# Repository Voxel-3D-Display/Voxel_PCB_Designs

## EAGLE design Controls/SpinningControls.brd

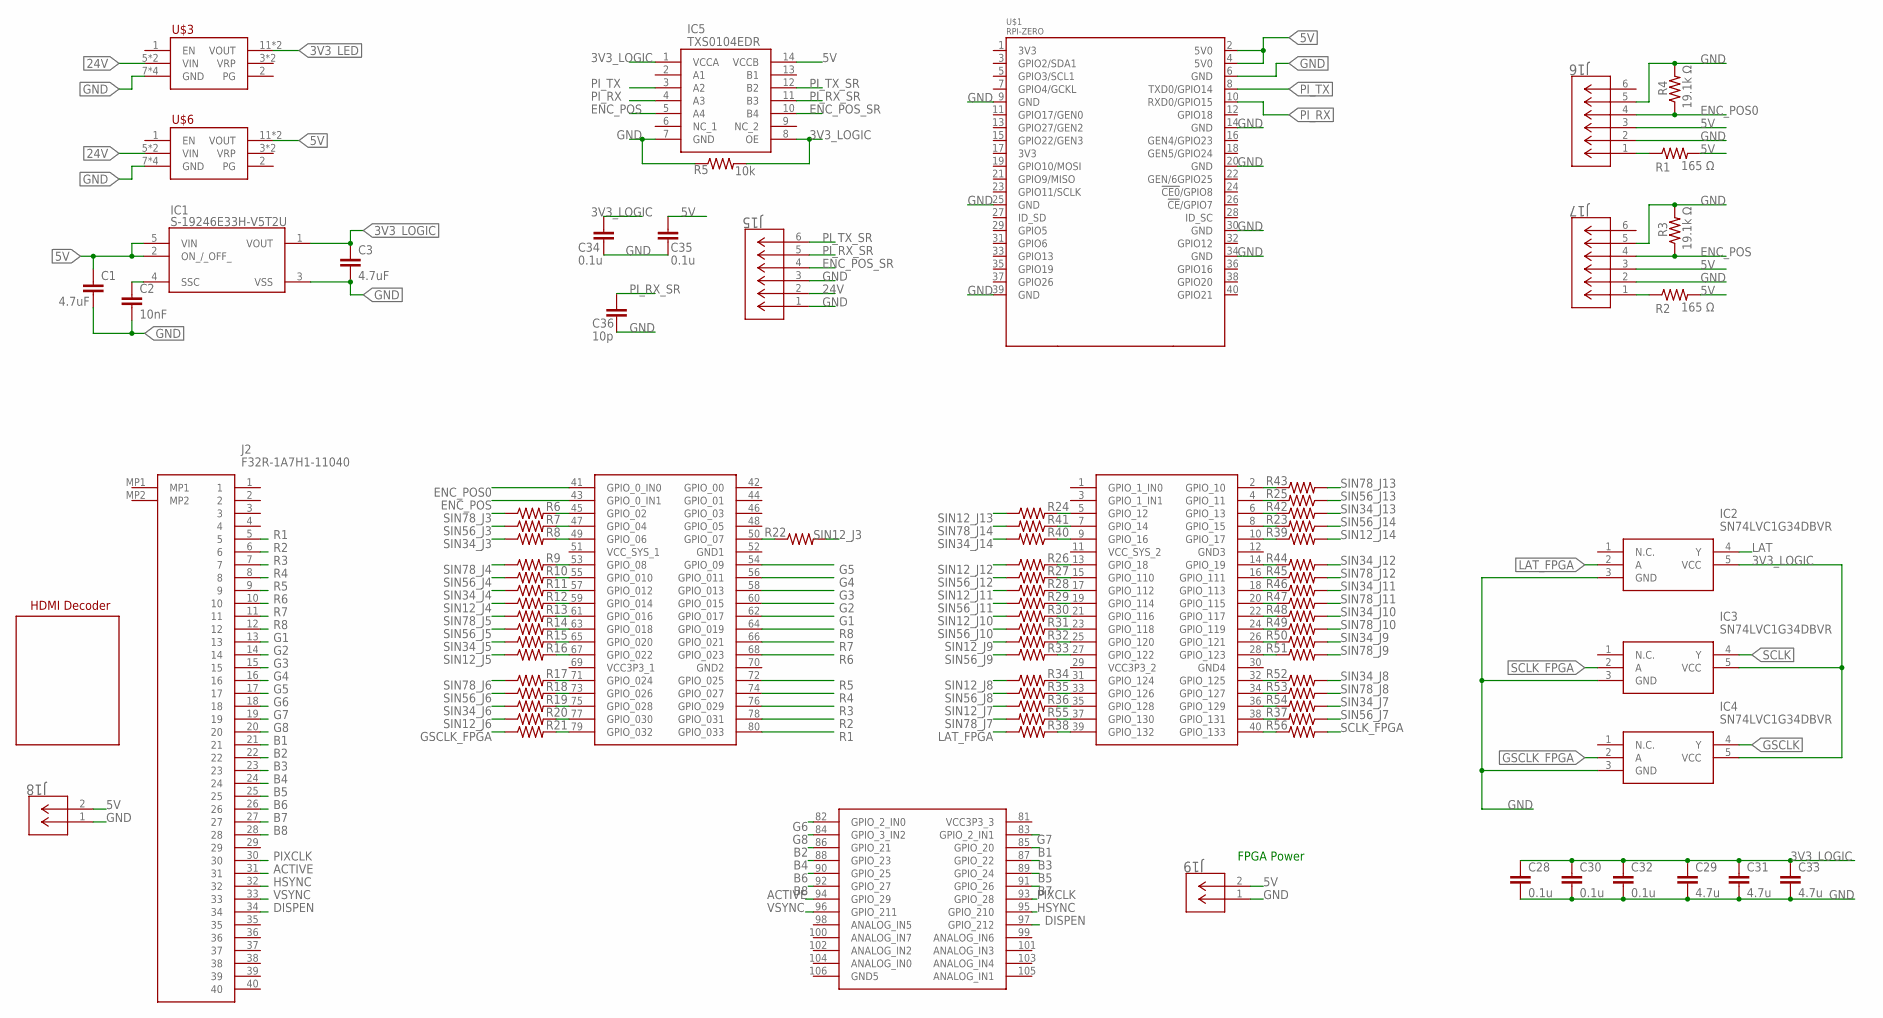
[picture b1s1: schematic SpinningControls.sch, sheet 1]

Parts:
C1, C3: 4.7uF; C0603
C2: 10nF; C0603
C28, C30, C32, C34, C35: 0.1u; C0603
C29, C31, C33: 4.7u; C0603
C36: 10p; C0603
FPGA: DE0-NANO
IC1: S-19246E33H-V5T2U; S19246E33HV5T2U
IC2, IC3, IC4: SN74LVC1G34DBVR; SOT95P280X145-5N
IC5: TXS0104EDR; SOIC127P600X175-14N
J2: F32R-1A7H1-11040; F32R1A7H111040
J15, J16, J17: 430450612; CON_430450612_MOL
J18, J19: 436500215; CON_436500215_MOL
R1, R2: 165 Ω; R0603
R3, R4: 19.1k Ω; R0603
R5: 10k; R0603
R6, R7, R8, R9, R10, R11, R12, R13, R14, R15, R16, R17, R18, R19, R20, R21, R22, R23, R24, R25, R26, R27, R28, R29, R30, R31, R32, R33, R34, R35, R36, R37, R38, R39, R40, R41, R42, R43, R44, R45, R46, R47, R48, R49, R50, R51, R52, R53, R54, R55, R56: R-US_R0402; R0402
U$1: RPI-ZERO; RASPBERRYPI_BASTELSTUBE_V13_RASPI_BOARD_B+_FULL
U$2: TFP401
U$3: 3V3_BUCK_REGULATOR; 2X06
U$6: 5V_BUCK_REGULATOR; 2X06

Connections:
3V3_LED: U$3.11 (VOUT), U$3.12 (VOUT); also elsewhere on the board
3V3_LOGIC: C3.1, C28.1, C29.1, C30.1, C31.1, C32.1, C33.1, C34.1, IC1.1 (VOUT), IC2.5 (VCC), IC3.5 (VCC), IC4.5 (VCC), IC5.1 (VCCA), IC5.8 (OE), R5.2; also elsewhere on the board
5V: C1.1, C35.1, IC1.2 (ON_/_OFF_), IC1.5 (VIN), IC5.14 (VCCB), J16.3, J17.3, J18.2, J19.2, R1.2, R2.2, U$1.2 (5V0), U$1.4 (5V0), U$6.11 (VOUT), U$6.12 (VOUT)
24V: J15.2, U$3.5 (VIN), U$3.6 (VIN), U$6.5 (VIN), U$6.6 (VIN)
ACTIVE: FPGA.94 (GPIO_29), J2.31
B1: FPGA.85 (GPIO_20), J2.21
B2: FPGA.86 (GPIO_21), J2.22
B3: FPGA.87 (GPIO_22), J2.23
B4: FPGA.88 (GPIO_23), J2.24
B5: FPGA.89 (GPIO_24), J2.25
B6: FPGA.90 (GPIO_25), J2.26
B7: FPGA.91 (GPIO_26), J2.27
B8: FPGA.92 (GPIO_27), J2.28
DISPEN: FPGA.97 (GPIO_212), J2.34
ENC_POS: FPGA.43 (GPIO_0_IN1), IC5.5 (A4), J17.4, R3.1
ENC_POS0: FPGA.41 (GPIO_0_IN0), J16.4, R4.1
ENC_POS_SR: IC5.10 (B4), J15.4
G1: FPGA.62 (GPIO_017), J2.13
G2: FPGA.60 (GPIO_015), J2.14
G3: FPGA.58 (GPIO_013), J2.15
G4: FPGA.56 (GPIO_011), J2.16
G5: FPGA.54 (GPIO_09), J2.17
G6: FPGA.82 (GPIO_2_IN0), J2.18
G7: FPGA.83 (GPIO_2_IN1), J2.19
G8: FPGA.84 (GPIO_3_IN2), J2.20
GND: C1.2, C2.2, C3.2, C28.2, C29.2, C30.2, C31.2, C32.2, C33.2, C34.2, C35.2, C36.2, IC1.3 (VSS), IC2.3 (GND), IC3.3 (GND), IC4.3 (GND), IC5.7 (GND), J15.1, J15.3, J16.2, J16.5, J17.2, J17.5, J18.1, J19.1, R3.2, R4.2, R5.1, U$1.6 (GND), U$1.9 (GND), U$1.14 (GND), U$1.20 (GND), U$1.25 (GND), U$1.30 (GND), U$1.34 (GND), U$1.39 (GND), U$3.7 (GND), U$3.8 (GND), U$3.9 (GND), U$3.10 (GND), U$6.7 (GND), U$6.8 (GND), U$6.9 (GND), U$6.10 (GND); also elsewhere on the board
GSCLK: IC4.4 (Y); also elsewhere on the board
GSCLK_FPGA: IC4.2 (A), R21.1
HSYNC: FPGA.95 (GPIO_210), J2.32
LAT: IC2.4 (Y); also elsewhere on the board
LAT_FPGA: IC2.2 (A), R38.1
unnamed: J16.1, R1.1
unnamed: FPGA.45 (GPIO_02), R6.2
unnamed: FPGA.50 (GPIO_07), R22.1
unnamed: C2.1, IC1.4 (SSC)
unnamed: FPGA.79 (GPIO_032), R21.2
unnamed: J17.1, R2.1
unnamed: FPGA.8 (GPIO_15), R23.2
unnamed: FPGA.5 (GPIO_12), R24.2
unnamed: FPGA.4 (GPIO_11), R25.2
unnamed: FPGA.9 (GPIO_16), R40.1
unnamed: FPGA.7 (GPIO_14), R41.1
unnamed: FPGA.6 (GPIO_13), R42.1
unnamed: FPGA.2 (GPIO_10), R43.1
unnamed: FPGA.13 (GPIO_18), R26.2
unnamed: FPGA.47 (GPIO_04), R7.2
unnamed: FPGA.49 (GPIO_06), R8.2
unnamed: FPGA.15 (GPIO_110), R27.2
unnamed: FPGA.53 (GPIO_08), R9.2
unnamed: FPGA.55 (GPIO_010), R10.2
unnamed: FPGA.57 (GPIO_012), R11.2
unnamed: FPGA.59 (GPIO_014), R12.2
unnamed: FPGA.61 (GPIO_016), R13.2
unnamed: FPGA.63 (GPIO_018), R14.2
unnamed: FPGA.65 (GPIO_020), R15.2
unnamed: FPGA.67 (GPIO_022), R16.2
unnamed: FPGA.17 (GPIO_112), R28.2
unnamed: FPGA.71 (GPIO_024), R17.2
unnamed: FPGA.73 (GPIO_026), R18.2
unnamed: FPGA.75 (GPIO_028), R19.2
unnamed: FPGA.77 (GPIO_030), R20.2
unnamed: FPGA.19 (GPIO_114), R29.2
unnamed: FPGA.21 (GPIO_116), R30.2
unnamed: FPGA.23 (GPIO_118), R31.2
unnamed: FPGA.25 (GPIO_120), R32.2
unnamed: FPGA.27 (GPIO_122), R33.2
unnamed: FPGA.31 (GPIO_124), R34.2
unnamed: FPGA.33 (GPIO_126), R35.2
unnamed: FPGA.35 (GPIO_128), R36.2
unnamed: FPGA.38 (GPIO_131), R37.2
unnamed: FPGA.39 (GPIO_132), R38.2
unnamed: FPGA.14 (GPIO_19), R44.1
unnamed: FPGA.16 (GPIO_111), R45.1
unnamed: FPGA.18 (GPIO_113), R46.1
unnamed: FPGA.20 (GPIO_115), R47.1
unnamed: FPGA.22 (GPIO_117), R48.1
unnamed: FPGA.24 (GPIO_119), R49.1
unnamed: FPGA.26 (GPIO_121), R50.1
unnamed: FPGA.28 (GPIO_123), R51.1
unnamed: FPGA.32 (GPIO_125), R52.1
unnamed: FPGA.34 (GPIO_127), R53.1
unnamed: FPGA.36 (GPIO_129), R54.1
unnamed: FPGA.37 (GPIO_130), R55.1
unnamed: FPGA.40 (GPIO_133), R56.1
unnamed: FPGA.10 (GPIO_17), R39.1
PIXCLK: FPGA.93 (GPIO_28), J2.30
PI_RX: IC5.4 (A3), U$1.10 (RXD0/GPIO15)
PI_RX_SR: C36.1, IC5.11 (B3), J15.5
PI_TX: IC5.3 (A2), U$1.8 (TXD0/GPIO14)
PI_TX_SR: IC5.12 (B2), J15.6
R1: FPGA.80 (GPIO_033), J2.5
R2: FPGA.78 (GPIO_031), J2.6
R3: FPGA.76 (GPIO_029), J2.7
R4: FPGA.74 (GPIO_027), J2.8
R5: FPGA.72 (GPIO_025), J2.9
R6: FPGA.68 (GPIO_023), J2.10
R7: FPGA.66 (GPIO_021), J2.11
R8: FPGA.64 (GPIO_019), J2.12
SCLK: IC3.4 (Y); also elsewhere on the board
SCLK_FPGA: IC3.2 (A), R56.2
SIN12_J3: R22.2; also elsewhere on the board
SIN12_J4: R12.1; also elsewhere on the board
SIN12_J5: R16.1; also elsewhere on the board
SIN12_J6: R20.1; also elsewhere on the board
SIN12_J7: R36.1; also elsewhere on the board
SIN12_J8: R34.1; also elsewhere on the board
SIN12_J9: R32.1; also elsewhere on the board
SIN12_J10: R30.1; also elsewhere on the board
SIN12_J11: R28.1; also elsewhere on the board
SIN12_J12: R26.1; also elsewhere on the board
SIN12_J13: R24.1; also elsewhere on the board
SIN12_J14: R39.2; also elsewhere on the board
SIN34_J3: R8.1; also elsewhere on the board
SIN34_J4: R11.1; also elsewhere on the board
SIN34_J5: R15.1; also elsewhere on the board
SIN34_J6: R19.1; also elsewhere on the board
SIN34_J7: R54.2; also elsewhere on the board
SIN34_J8: R52.2; also elsewhere on the board
SIN34_J9: R50.2; also elsewhere on the board
SIN34_J10: R48.2; also elsewhere on the board
SIN34_J11: R46.2; also elsewhere on the board
SIN34_J12: R44.2; also elsewhere on the board
SIN34_J13: R42.2; also elsewhere on the board
SIN34_J14: R40.2; also elsewhere on the board
SIN56_J3: R7.1; also elsewhere on the board
SIN56_J4: R10.1; also elsewhere on the board
SIN56_J5: R14.1; also elsewhere on the board
SIN56_J6: R18.1; also elsewhere on the board
SIN56_J7: R37.1; also elsewhere on the board
SIN56_J8: R35.1; also elsewhere on the board
SIN56_J9: R33.1; also elsewhere on the board
SIN56_J10: R31.1; also elsewhere on the board
SIN56_J11: R29.1; also elsewhere on the board
SIN56_J12: R27.1; also elsewhere on the board
SIN56_J13: R25.1; also elsewhere on the board
SIN56_J14: R23.1; also elsewhere on the board
SIN78_J3: R6.1; also elsewhere on the board
SIN78_J4: R9.1; also elsewhere on the board
SIN78_J5: R13.1; also elsewhere on the board
SIN78_J6: R17.1; also elsewhere on the board
SIN78_J7: R55.2; also elsewhere on the board
SIN78_J8: R53.2; also elsewhere on the board
SIN78_J9: R51.2; also elsewhere on the board
SIN78_J10: R49.2; also elsewhere on the board
SIN78_J11: R47.2; also elsewhere on the board
SIN78_J12: R45.2; also elsewhere on the board
SIN78_J13: R43.2; also elsewhere on the board
SIN78_J14: R41.2; also elsewhere on the board
VSYNC: FPGA.96 (GPIO_211), J2.33

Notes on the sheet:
FPGA Power

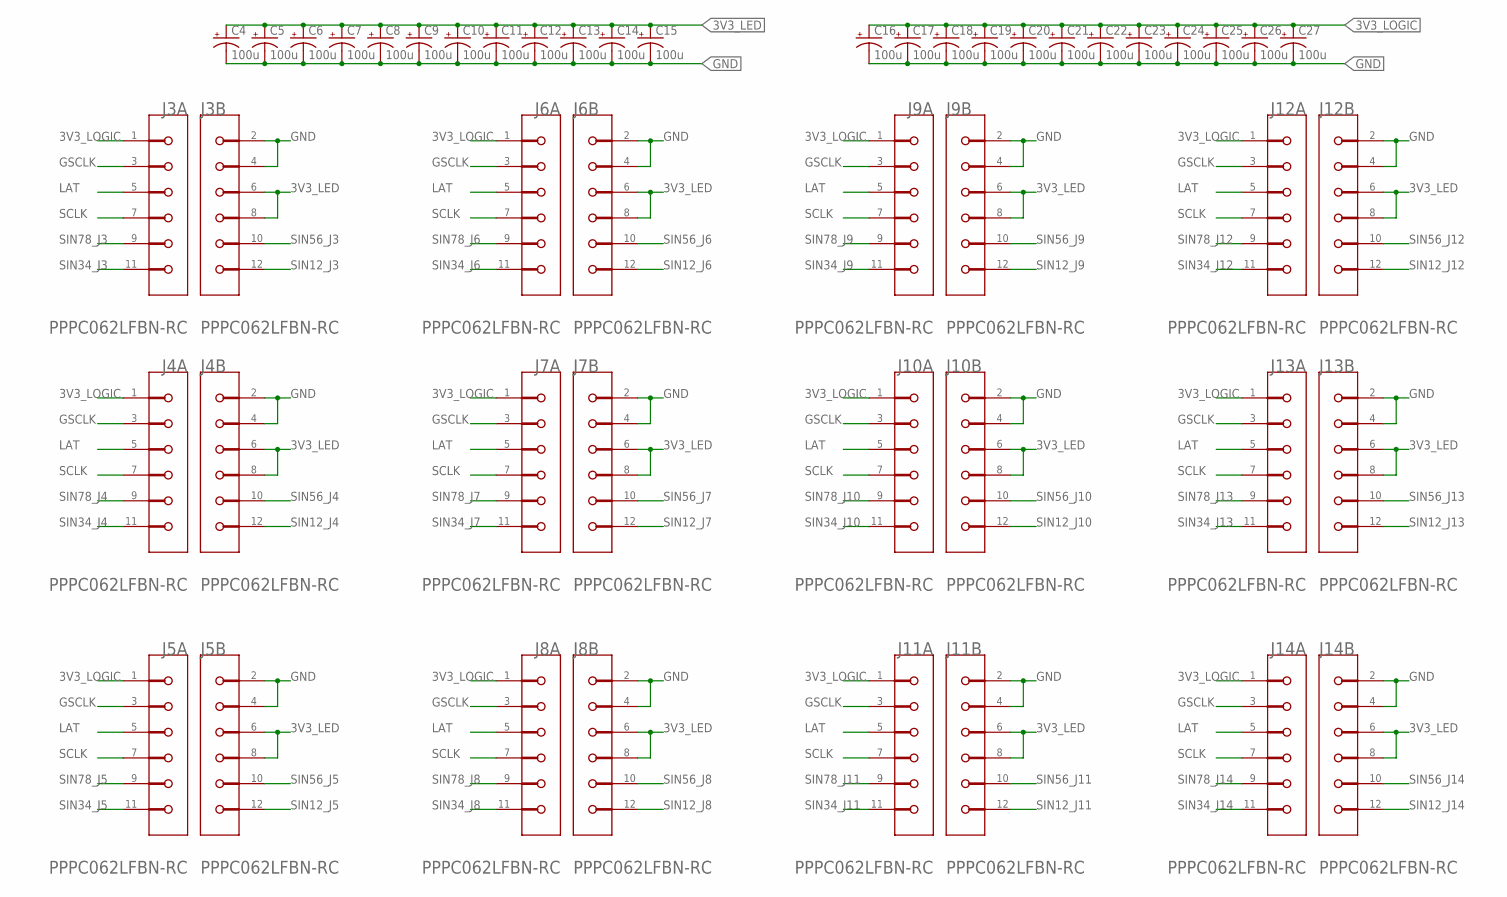
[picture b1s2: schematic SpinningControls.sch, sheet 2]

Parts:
C4, C5, C6, C7, C8, C9, C10, C11, C12, C13, C14, C15, C16, C17, C18, C19, C20, C21, C22, C23, C24, C25, C26, C27: 100u; E2-5
J3, J4, J5, J6, J7, J8, J9, J10, J11, J12, J13, J14: SULLINS_PPPC062LFBN-RCSULLINS_PPPC062LFBN-RC_0_0; SULLINS_PPPC062LFBN-RC_0

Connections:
3V3_LED: C4.+, C5.+, C6.+, C7.+, C8.+, C9.+, C10.+, C11.+, C12.+, C13.+, C14.+, C15.+, J3.6, J3.8, J4.6, J4.8, J5.6, J5.8, J6.6, J6.8, J7.6, J7.8, J8.6, J8.8, J9.6, J9.8, J10.6, J10.8, J11.6, J11.8, J12.6, J12.8, J13.6, J13.8, J14.6, J14.8; also elsewhere on the board
3V3_LOGIC: C16.+, C17.+, C18.+, C19.+, C20.+, C21.+, C22.+, C23.+, C24.+, C25.+, C26.+, C27.+, J3.1, J4.1, J5.1, J6.1, J7.1, J8.1, J9.1, J10.1, J11.1, J12.1, J13.1, J14.1; also elsewhere on the board
GND: C4.-, C5.-, C6.-, C7.-, C8.-, C9.-, C10.-, C11.-, C12.-, C13.-, C14.-, C15.-, C16.-, C17.-, C18.-, C19.-, C20.-, C21.-, C22.-, C23.-, C24.-, C25.-, C26.-, C27.-, J3.2, J3.4, J4.2, J4.4, J5.2, J5.4, J6.2, J6.4, J7.2, J7.4, J8.2, J8.4, J9.2, J9.4, J10.2, J10.4, J11.2, J11.4, J12.2, J12.4, J13.2, J13.4, J14.2, J14.4; also elsewhere on the board
GSCLK: J3.3, J4.3, J5.3, J6.3, J7.3, J8.3, J9.3, J10.3, J11.3, J12.3, J13.3, J14.3; also elsewhere on the board
LAT: J3.5, J4.5, J5.5, J6.5, J7.5, J8.5, J9.5, J10.5, J11.5, J12.5, J13.5, J14.5; also elsewhere on the board
SCLK: J3.7, J4.7, J5.7, J6.7, J7.7, J8.7, J9.7, J10.7, J11.7, J12.7, J13.7, J14.7; also elsewhere on the board
SIN12_J3: J3.12; also elsewhere on the board
SIN12_J4: J4.12; also elsewhere on the board
SIN12_J5: J5.12; also elsewhere on the board
SIN12_J6: J6.12; also elsewhere on the board
SIN12_J7: J7.12; also elsewhere on the board
SIN12_J8: J8.12; also elsewhere on the board
SIN12_J9: J9.12; also elsewhere on the board
SIN12_J10: J10.12; also elsewhere on the board
SIN12_J11: J11.12; also elsewhere on the board
SIN12_J12: J12.12; also elsewhere on the board
SIN12_J13: J13.12; also elsewhere on the board
SIN12_J14: J14.12; also elsewhere on the board
SIN34_J3: J3.11; also elsewhere on the board
SIN34_J4: J4.11; also elsewhere on the board
SIN34_J5: J5.11; also elsewhere on the board
SIN34_J6: J6.11; also elsewhere on the board
SIN34_J7: J7.11; also elsewhere on the board
SIN34_J8: J8.11; also elsewhere on the board
SIN34_J9: J9.11; also elsewhere on the board
SIN34_J10: J10.11; also elsewhere on the board
SIN34_J11: J11.11; also elsewhere on the board
SIN34_J12: J12.11; also elsewhere on the board
SIN34_J13: J13.11; also elsewhere on the board
SIN34_J14: J14.11; also elsewhere on the board
SIN56_J3: J3.10; also elsewhere on the board
SIN56_J4: J4.10; also elsewhere on the board
SIN56_J5: J5.10; also elsewhere on the board
SIN56_J6: J6.10; also elsewhere on the board
SIN56_J7: J7.10; also elsewhere on the board
SIN56_J8: J8.10; also elsewhere on the board
SIN56_J9: J9.10; also elsewhere on the board
SIN56_J10: J10.10; also elsewhere on the board
SIN56_J11: J11.10; also elsewhere on the board
SIN56_J12: J12.10; also elsewhere on the board
SIN56_J13: J13.10; also elsewhere on the board
SIN56_J14: J14.10; also elsewhere on the board
SIN78_J3: J3.9; also elsewhere on the board
SIN78_J4: J4.9; also elsewhere on the board
SIN78_J5: J5.9; also elsewhere on the board
SIN78_J6: J6.9; also elsewhere on the board
SIN78_J7: J7.9; also elsewhere on the board
SIN78_J8: J8.9; also elsewhere on the board
SIN78_J9: J9.9; also elsewhere on the board
SIN78_J10: J10.9; also elsewhere on the board
SIN78_J11: J11.9; also elsewhere on the board
SIN78_J12: J12.9; also elsewhere on the board
SIN78_J13: J13.9; also elsewhere on the board
SIN78_J14: J14.9; also elsewhere on the board

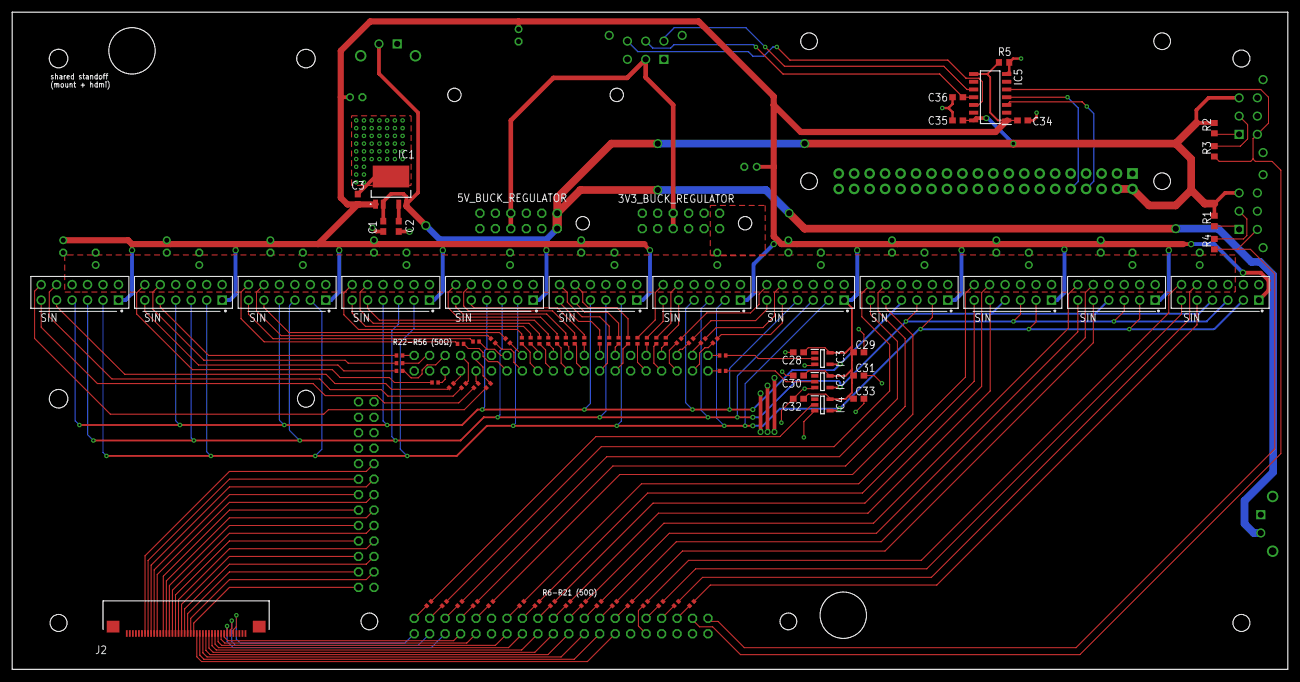
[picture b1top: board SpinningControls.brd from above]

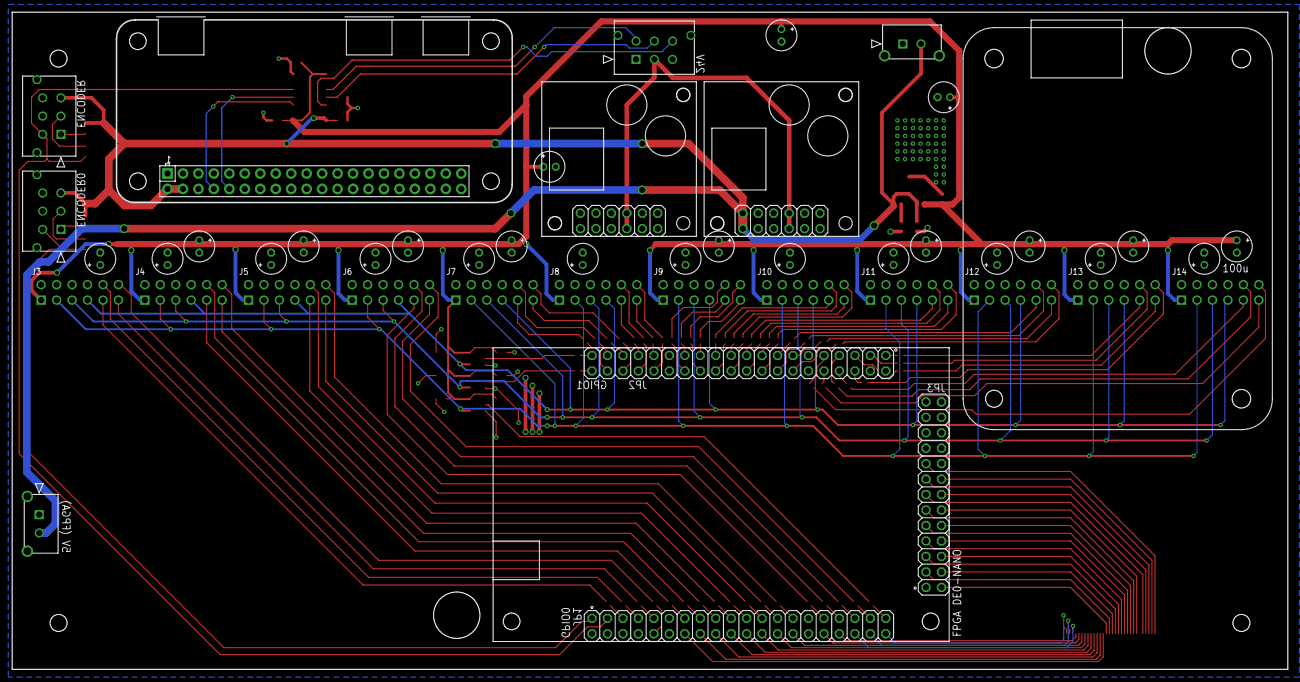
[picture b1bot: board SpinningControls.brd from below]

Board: 2 copper layers, 209.6 x 107.9 mm, 120 parts (36 on the bottom side), 149 nets.

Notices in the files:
parts and their libraries:
COPYRIGHT: Copyright (C) 2022 Ultra Librarian. All rights reserved.
